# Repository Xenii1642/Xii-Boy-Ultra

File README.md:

Have you ever dreamed of a portable Wii before? Or even one with Wifi and Bluetooth integration? 
What about analog triggers, and RVL-DD? Or the Wire-free system that allows you to entirely dissasemble the system without any soldering iron?

Well, I'm here to tell that that dream came true, and I called it the Xii-Boy Ultra. 

This new Xii-Boy Ultra is the third and latest edition of my Xii-Boy design I first started almost 2 years ago. 
It comes with all the latest features everyone has been dreaming of for years. This means many crazy mods like the RVL-DD,
or all the cool stuff over the [4Layer Technologies](https://4layertech.com/), analog triggers for full Gamecube games compatibility,
optional WiFi and Bluetooth functionalities to play online or to use an original WiiMote controller and so many others. 
Everything is nicely packed up inside that little portable, 25% smaller than the previous Gboy III. 

Further technical specifications can be found on the following links:
- [Xii-Boy Ultra Worklog](https://bitbuilt.net/forums/threads/xii-boy-ultra-v3.6641/)
- [Xii-Boy Ultra Beta Release](https://bitbuilt.net/forums/threads/the-xii-boy-ultra-v3-beta-release.6918/)
- [Xii-Boy Ultra REV 2 Release](https://bitbuilt.net/forums/threads/xii-boy-ultra-rev-2.7108/#post-74825)

I've been working on the possibility to offer kits to the community for the last 7 months. 
Over that time, the design received a lot of changes to improve reliability, compatibility and overall quality of the build. 
This branche of the repository is all about the latest Revision 2 of the design. It is made with the kits in mind, and is the revision the 6 beta testers will receive for a review.

I personally assembled that latest revision by myself, and it has been confirmed working, reason why I'm sharing everything here!

⚠️ Due to the complexity nature of the build, and the knowledge it requires to build or use, I can't be held responsible for any issues, accidents or injuries that may occur. 
This Beta Reivision might also come with design flaws or issues. Please contact me of the Xii-Boy Team in case you notice any. ⚠️

# Availability
For now, the design cannot be purchased as a kit. This will hopefully change in a few months, even though I have no idea of when the kits will become available. Stay tuned on my Worklog.
This means the only alternative is to source all the parts on yourself and to assemble everything on your side. 

Please take a look at the following points carefully. 

# Parts
Everything you need to build your own can be found in the [Xii-Boy Ultra Parts list](https://github.com/Xenii1642/Xii-Boy-Ultra/blob/REV-2.0/Parts-List.pdf) file. 
Please note that most of the articles are only available through Aliexpress, which might not be ideal due to the tariffs situation.

🔋For the batteries, I personally recommend those: [Recommended Batteries](https://www.akkuteile.de/samsung-inr18650-35e-3-6v-3-7v-3500mah-pluspol-flach_100631_3391)
There is plenty of website that sell batteries. You should aquire them from a source you're confident with. If you live in Europe, I highly recommend [Akkuteile](https://www.akkuteile.de/). 
It's a German website and I always been pleased by their services. ⚠️ Be careful to order them from a reliable source to avoid counterfeiting. Fake batteries can be extremly dangerous. ⚠️

# PCBs
As all the build, the Xii-Boy Ultra PCBs are all open-sourced. If you just want to order them, you can use the [Gerber files](https://github.com/Xenii1642/Xii-Boy-Ultra/tree/REV-2.0/Gerbers).
Multiple manufacters work, but I suggest either [JLCPCB](https://jlcpcb.com/) or [PCBWay](https://pcbway.com) for that build.

You can also make edits using the [Kicad 9 files](https://github.com/Xenii1642/Xii-Boy-Ultra/tree/REV-2.0/KiCad%20Files).

For the components, everything is listed in the [PCB BOM File](https://github.com/Xenii1642/Xii-Boy-Ultra/blob/REV-2.0/PCB-BOM.pdf). 
Some articles can only be found on Digikey, reason why all the parts of this list come from them. 

Ordering PCB is one of the most important step, and you should really make sure to enable the correct settings while ordering, otherwise you could run into multiple issues.
Many of the following boards **will not** work with the default settings, so please make sure to order them with the proper settings 👍

Here is a list of all the settings for each board:
### [**Main PCB (XBU-001)**:](https://github.com/Xenii1642/Xii-Boy-Ultra/blob/REV-2.0/Gerbers/Main%20PCB.zip)
- Material: FR4
- Specify Stackup: YES
- Stackup profile: JLC04161H-7628
- Thickness: 1.6mm
  
### [**Xii-DD (XBU-002)**:](https://github.com/Xenii1642/Xii-Boy-Ultra/blob/REV-2.0/Gerbers/Xii-DD.zip)
- Material: FR4
- Thickness: 1.2mm
  
### [**Controller PCB (XBU-003)**:](https://github.com/Xenii1642/Xii-Boy-Ultra/blob/REV-2.0/Gerbers/Controller%20PCB.zip)
- Material: FR4
- Thickness: 1.6mm
- Surface finish: ENIG

### [**Xii-Flex Ultra (XBU-004)**:](https://github.com/Xenii1642/Xii-Boy-Ultra/blob/REV-2.0/Gerbers/Xii-Flex%20Ultra.zip)
- Material: Flex
- Thickness: 0.12mm (💡0.11mm also works, but it's way riskier and more fragile according to some people. I personnaly didn't notice a lot of differences.)
- Stiffener: YES, Polyimide 0.2mm

### [**Trigger PCB (XBU-005)**:](https://github.com/Xenii1642/Xii-Boy-Ultra/blob/REV-2.0/Gerbers/Trigger%20PCB.zip)
- Material: FR4
- Thickness: 1mm

### [**Xii-Strip (XBU-006)**:](https://github.com/Xenii1642/Xii-Boy-Ultra/blob/REV-2.0/Gerbers/Xii-Strip.zip)
- Material: FR4
- Thickness: 0.8mm

### [**40p Shielded FFC (XBU-007)**:](https://github.com/Xenii1642/Xii-Boy-Ultra/blob/REV-2.0/Gerbers/Shielded%20FFC.zip)
- Material: Flex
- Thickness: 0.12 (💡For that baord, 0.11mm also works well)
- Stiffener: YES, Polyimide 0.2mm

Color and can be changed, but make sure to only modify the settings you're confident with. 

# Shell
The shell files are all available in the [3D Section](https://github.com/Xenii1642/Xii-Boy-Ultra/tree/REV-2.0/3D).
Since STL can only be ordered and not edited, I decided to only share the STEP files, which allow both editing and ordering without any issues. 

Some files have minors changes, so make sure to read the following points to understand the one you need for your use.
### **FDM**:
If you have a classic FDM 3D Printer, or planned printing the case on one, you should use the [FDM](https://github.com/Xenii1642/Xii-Boy-Ultra/tree/REV-2.0/3D/Shell/FDM) version of the files.
Screen's friction fit doesn't have the same tolerances on FDM and SLS/SLA. Choosing the wrong file might occur into the screen to not fit at all, or to not stick at all, causing it to fall.

### **SLS-SLA**:
If you planned ordering the case through [JLC3DP](https://jlc3dp.com/) or [PCBWay](https://www.pcbway.com/) using Nylon (SLS or MJF) or Resin (SLA), or simply printing one yourself with a resin printer,
you should use the [Resin & Nylon](https://github.com/Xenii1642/Xii-Boy-Ultra/tree/REV-2.0/3D/Shell/SLS-SLA) file.
Considering the shell is much smoother here, normal Friction Fit doesn't work well, and the screen might pop off pretty easily.
To avoid that, those versions have a Super Friction Fit technology, which mimic the FDM layers and make the screen strongly attached into the shell.

⚠️ Disclamer: SLA + spray varnish is something to avoid, since it adds enough volume to make the parts to not fit properly. 

### **Stands**
You can also find the Xii-Boy Ultra stands in the [stands folder](https://github.com/Xenii1642/Xii-Boy-Ultra/tree/REV-2.0/3D/Stands) or on my Printables account: [Xii-Boy Ultra stands - Printables](https://www.printables.com/model/1307105-xii-boy-ultra-stands)
One of them has a slot for the [XiiSBar](https://github.com/Xenii1642/XiiSBar), which allows you to play game with the IR pointer (original WiiMote pointing system)

# Software
The Xii-Boy Ultra runs on RVLoader, a wonderful homebrew app made by Aurelio over the BitBuilt forum. However, it needs to be slightly modified for all the Xii-Boy Ultra features to work properly.

You'll find all the new files you need to update in the [Software](https://github.com/Xenii1642/Xii-Boy-Ultra/tree/REV-2.0/Software) section of the repository.

⚠️ Those files are tempoary and have been modified for the Xii-Boy Ultra only. They might contain issues or instablities. Update at your own risks. ⚠️
### [GCPlus2.0Update.hex](https://github.com/Xenii1642/Xii-Boy-Ultra/blob/main/Software/GCPlus2.0Update.hex)
This file is used to update the GC+ 2 from [4LayerTech](https://4layertech.com/) with a new version compatible with the Xii-Boy Ultra analog trigger system.
To update your GC+ 2.0, simply copy/paste that file in the root of your Xii-Boy Ultra µSD card.

### [boot.dol](https://github.com/Xenii1642/Xii-Boy-Ultra/blob/main/Software/boot.dol):
This files is used to add Volume and Brightness over buttons in Gamecube games.
To add those features, simply drag and replace the original file in `/apps/Nintendont`.

### [LCDDriver.bit](https://github.com/Xenii1642/Xii-Boy-Ultra/blob/main/Software/LCDDriver.bit)
This file is used to flash the DD software when booting. The original one, present by default in RVLoader contains a little issue with i2C.
It results into random crashes and volume or brightness control interferances. This file also removes the whine coil noise the old DD bitstream caused.
To install it, you just have to replace the original file in the root of your µSD card. ⚠️ This file or the previous one is necessary for the portable to boot ⚠️

### [hud.elf](https://github.com/Xenii1642/Xii-Boy-Ultra/blob/main/Software/hud.elf)
Like boot.dol, this file is used to add Volume and Brightness over buttons in Wii games.
To add those features, simply drag and replace the original file in `/rvloader/Hiidra/modules`

Once everything has been installed, safety eject your µSD card / Xii-Boy Ultra console.
Boot it up and go to `Settings` --> `Controller` --> `Firmware Update`
If everything has been done correctly, your Xii-Boy Ultra should be udpated.
Set your `Triggers mode` to `Analog` and press `Save Config`
Reboot your device and go to `Settings` --> `Controller` --> `Buttons Tester`
You should now see all the buttons and the analog triggers working!

# General Software Setting:
- In `Power` --> `Charge Settings`, `Battery Capacity` needs to be set at 7000mAh (or the capacity of one cell *2 `3500mAh *2 = 7000mAh`)
- `Charging Current` should be set at 3520mA
- `Precharge` and `Termination current` should be set at 128mA
- `Charge Voltage` should be set at 4200mV
- In `Misc Settings`, you need to change `Status LED type:` to `Adressable Type B`
- in `Audio`, `Volume control system` needs to be set to Buttons.
💡You can adapt all the settings depends on you. I personally set the `Status LED Intensity` to 5 and the `Rumble Intensity` to 60.

💡Make sure to test all the features, you should launch a Wii and a GameCube game, to make sure everything is working fine.

# Revisions
- REV0 - 1/1/2025 (First prototype not available)
- [REV1](https://github.com/Xenii1642/Xii-Boy-Ultra/tree/REV-1.0) - 18/5/2025 (Fixes the previous issues, first released revision)
- [REV2](https://github.com/Xenii1642/Xii-Boy-Ultra/tree/REV-2.0) - 16/11/2025 CURRENT (Fixes all the previous issues, removes pogo pins and upgrade a lot the reliability)

# Credits
Time to mention everybody who helped along the project!
- The Xii-Boy Team (JamesPi, BryceShaw, and I)
- YveltalGriffin (Help about PCB Design)
- Aurelio (RVLoader devloppement and software help) 
- All the Beta Testers (Modding Marius, Supertazon, YveltalGriffin, Macho Nacho, JamesPi, JoshsJunk05) 👍
  
# License
All Xii-Boy Ultra revisions are released under the CERN-OHL-S-2.0 license. 
This license allows you to:
- Study
- Modify
- Manufacture
- Sell
- Distribute

Any modified versions of derivatives must also remain open-source under **the same, unmodified license**
You must also properly credit the original creators when reusing or redistributing these files.

# Support
Due to the early Beta Release of the Xii-Boy Ultra, the design might contain issues, design flaws or other things.
This new REV2 corrected **all** the issues the previous revision had. But it doesn't mean it doesn't contain any. 

If you notice any issues, or things that could/should me updated, or even general recommendation, feel free to reach out for letting me know.
You can also ask help over the BitBuilt community (Discord server or forums), and I'd be happy to help. 

I'd also be grateful to receive feeback of the design. You can freely say what you thought about it, what you liked, disliked, etc.

Thanks a lot for the support and the help! Your feeback help a lot to make this product as perfect as possible!

I wish you all the best. Have fun!

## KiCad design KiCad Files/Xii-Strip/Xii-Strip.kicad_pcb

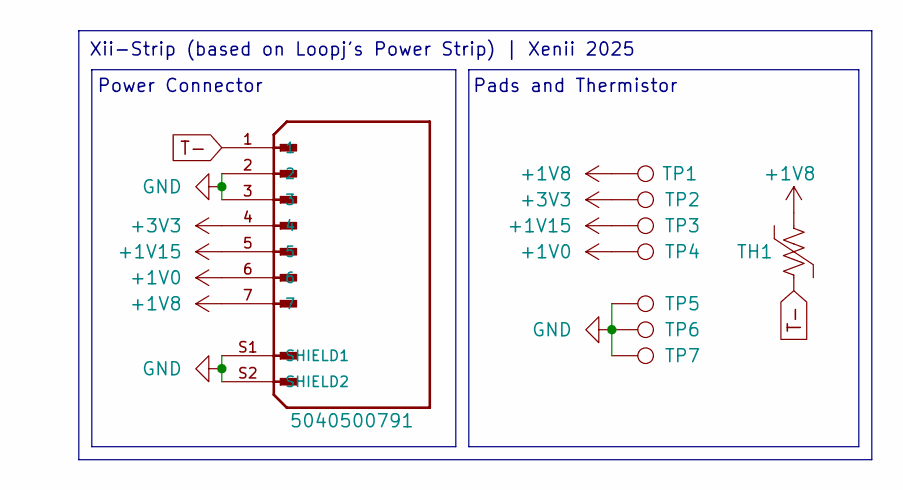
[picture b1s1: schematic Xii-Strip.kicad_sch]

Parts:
J1: 5040500791; MOLEX_5040500791; PARTREV B
TH1: Thermistor_US; R_0603_1608Metric
TP1, TP2, TP3, TP4, TP5, TP6, TP7: TestPoint; Xii-Strip-Power-Pad

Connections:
+1V0: J1.6, TP4.1
+1V8: J1.7, TH1.2, TP1.1
+1V15: J1.5, TP3.1
+3V3: J1.4, TP2.1
GND: J1.2, J1.3, J1.S1 (SHIELD1), J1.S2 (SHIELD2), TP5.1, TP6.1, TP7.1
T-: J1.1, TH1.1

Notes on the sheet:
Power Connector
Xii-Strip (based on Loopj's Power Strip) | Xenii 2025
Pads and Thermistor

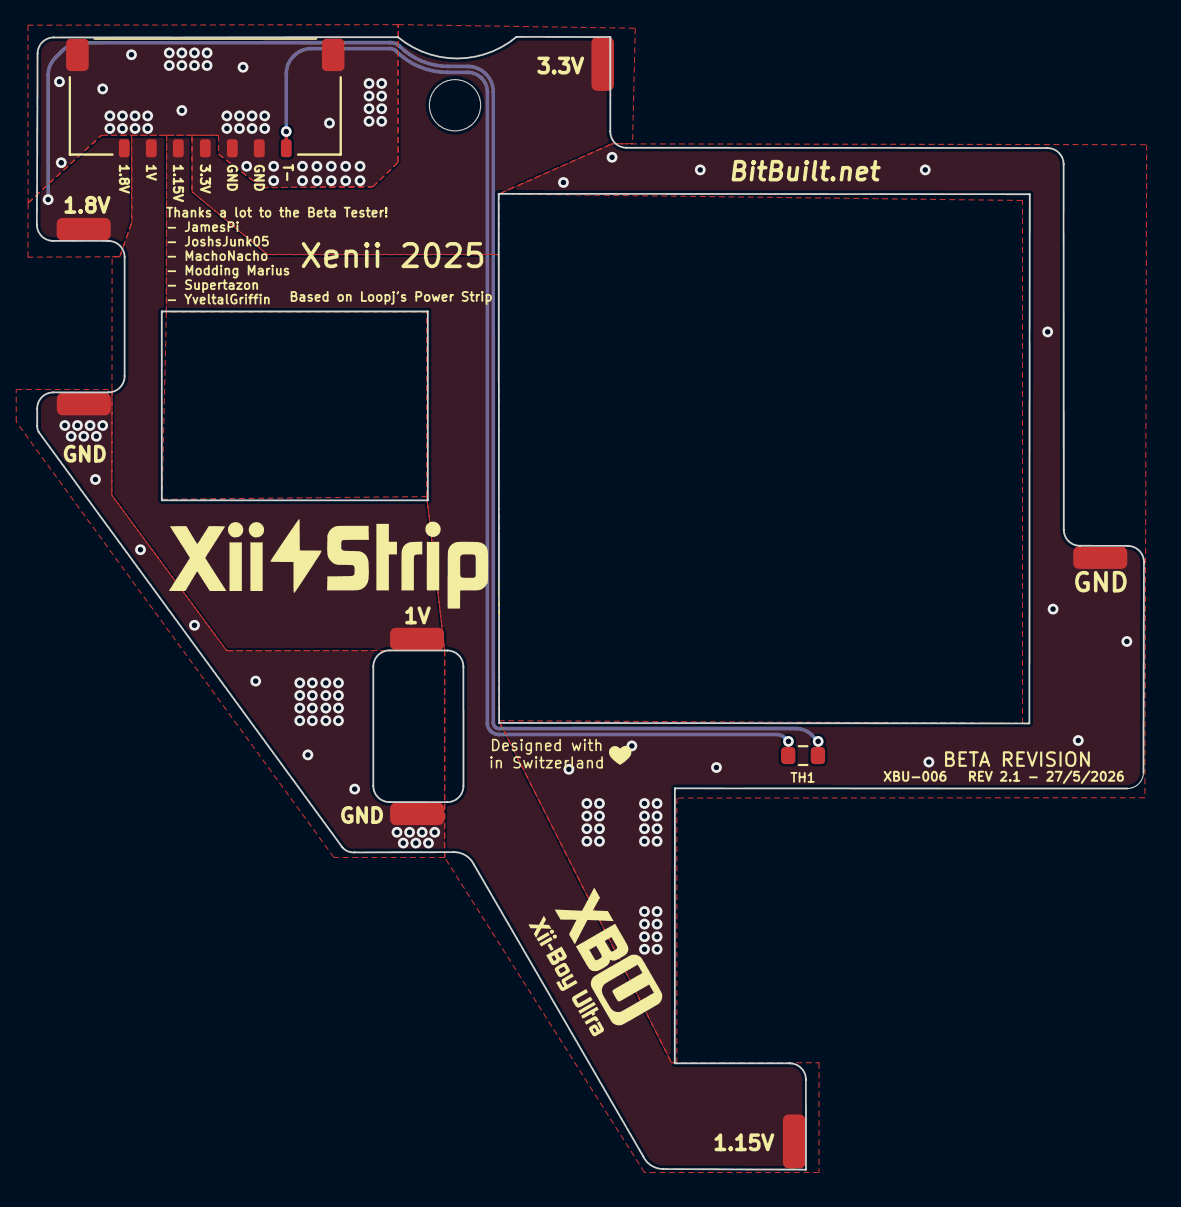
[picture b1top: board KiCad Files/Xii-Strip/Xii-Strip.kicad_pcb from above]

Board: 2 copper layers, 61.5 x 62.9 mm, 9 parts (0 on the bottom side), 6 nets.

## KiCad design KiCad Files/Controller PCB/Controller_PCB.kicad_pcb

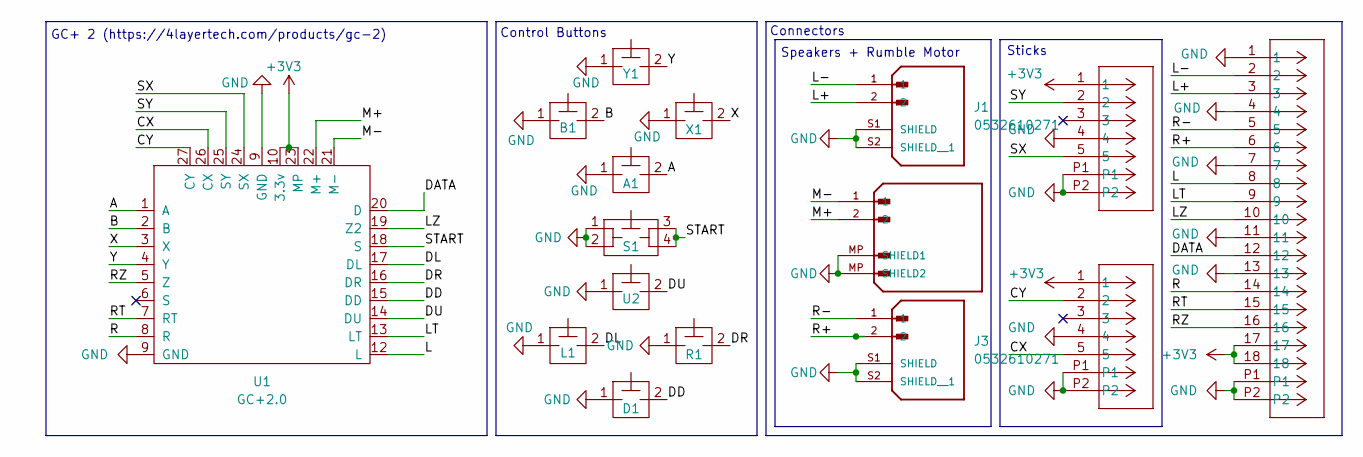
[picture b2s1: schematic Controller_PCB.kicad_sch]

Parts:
A1: DSLPad-Final
B1: DSLPad-Final
D1: DSLPad-Final
J1, J3: 0532610271; MOLEX_0532610271; PARTREV J
J2: 5037630291; MOLEX_5037630291; PARTREV B
J4, J5: 5051100592; CON_5051100592_MOL
J7: 5051101892; CON_5051101892_MOL
L1: DSLPad-Final
R1: DSLPad-Final
S1: SW_TL3315NF250Q
U1: GC+2.0
U2: DSLPad-Final
X1: DSLPad-Final
Y1: DSLPad-Final

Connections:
+3V3: J4.1, J5.1, J7.17, J7.18, U1.10 (3.3v), U1.23 (MP)
/A: A1.2, U1.1 (A)
/B: B1.2, U1.2 (B)
/CX: J5.5, U1.26 (CX)
/CY: J5.2, U1.27 (CY)
/DATA: J7.12, U1.20 (D)
/DD: D1.2, U1.15 (DD)
/DL: L1.2, U1.17 (DL)
/DR: R1.2, U1.16 (DR)
/DU: U1.14 (DU), U2.2
/L: J7.8, U1.12 (L)
/L+: J1.2, J7.3
/L-: J1.1, J7.2
/LT: J7.9, U1.13 (LT)
/LZ: J7.10, U1.19 (Z2)
/M+: J2.2, U1.22 (M+)
/M-: J2.1, U1.21 (M-)
/R: J7.14, U1.8 (R)
/R+: J3.2, J7.6
/R-: J3.1, J7.5
/RT: J7.15, U1.7 (RT)
/RZ: J7.16, U1.5 (Z)
/START: S1.3, S1.4, U1.18 (S)
/SX: J4.5, U1.24 (SX)
/SY: J4.2, U1.25 (SY)
/X: U1.3 (X), X1.2
/Y: U1.4 (Y), Y1.2
GND: A1.1, B1.1, D1.1, J1.S1 (SHIELD), J1.S2 (SHIELD__1), J2.MP (SHIELD1), J3.S1 (SHIELD), J3.S2 (SHIELD__1), J4.4, J4.P1, J4.P2, J5.4, J5.P1, J5.P2, J7.1, J7.4, J7.7, J7.11, J7.13, J7.P1, J7.P2, L1.1, R1.1, S1.1, S1.2, U1.9 (GND), U2.1, X1.1, Y1.1

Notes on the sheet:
GC+ 2 (https://4layertech.com/products/gc-2)
Speakers + Rumble Motor
Sticks
Control Buttons
Connectors

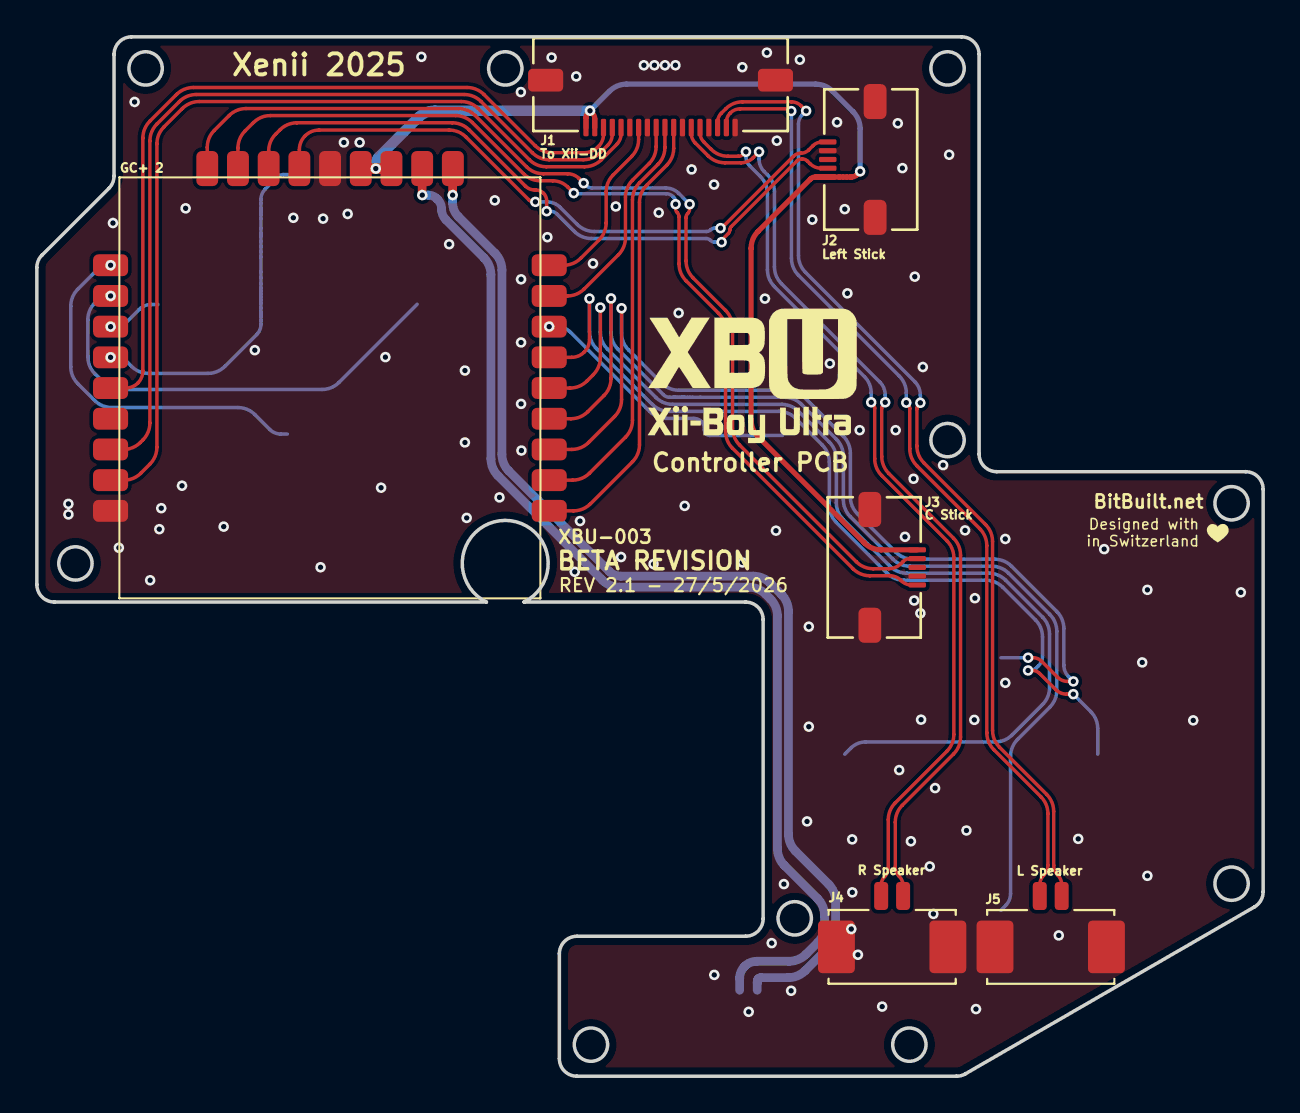
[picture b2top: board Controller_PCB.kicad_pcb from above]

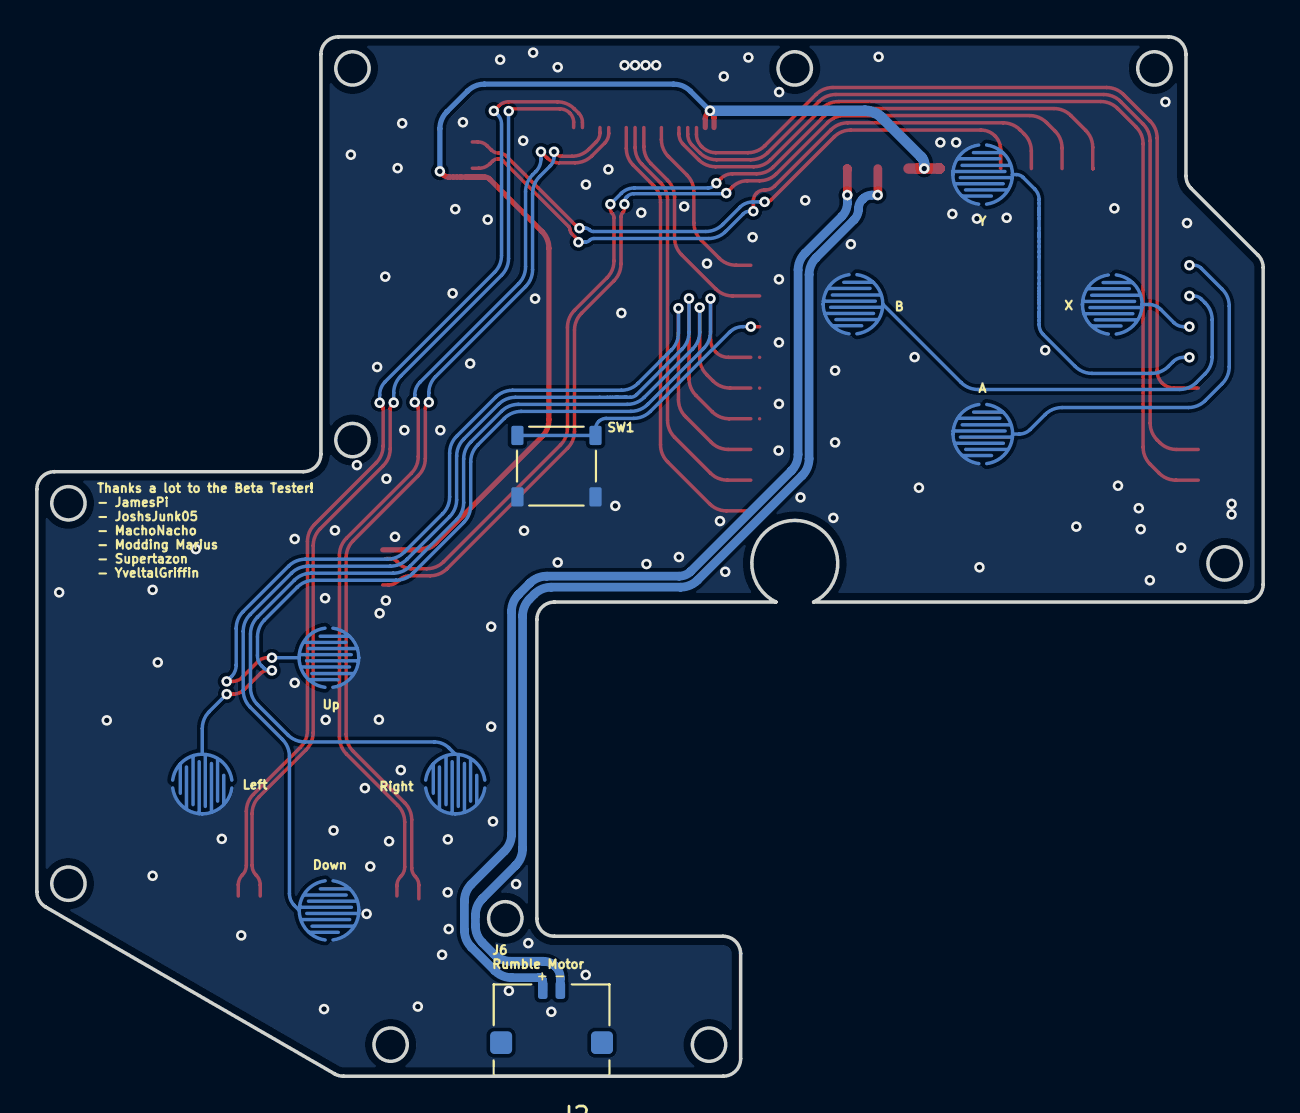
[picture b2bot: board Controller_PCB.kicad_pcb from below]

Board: 2 copper layers, 69.9 x 59.2 mm, 16 parts (10 on the bottom side), 28 nets.

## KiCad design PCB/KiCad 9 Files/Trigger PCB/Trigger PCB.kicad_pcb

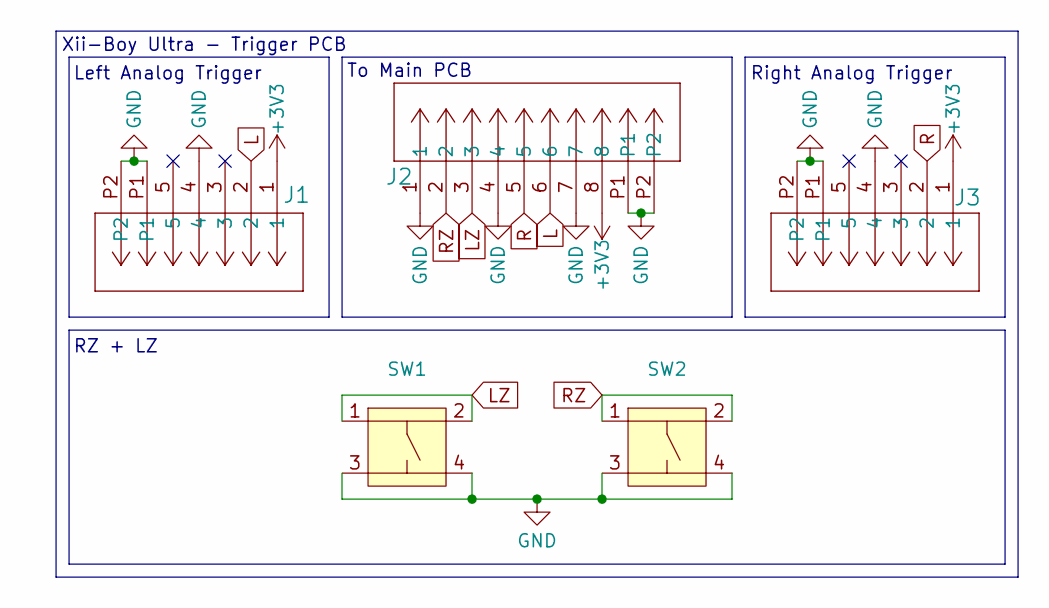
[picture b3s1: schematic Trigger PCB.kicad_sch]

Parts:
J1, J3: 5051100592; CON_5051100592_MOL
J2: 5051100892; CON_5051100892_MOL
SW1, SW2: KS201G

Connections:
+3V3: J1.1, J2.8, J3.1
GND: J1.4, J1.P1, J1.P2, J2.1, J2.4, J2.7, J2.P1, J2.P2, J3.4, J3.P1, J3.P2, SW1.3, SW1.4, SW2.3, SW2.4
L: J1.2, J2.6
LZ: J2.3, SW1.1, SW1.2
R: J2.5, J3.2
RZ: J2.2, SW2.1, SW2.2

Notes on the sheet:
RZ + LZ
Left Analog Trigger
To Main PCB
Xii-Boy Ultra - Trigger PCB
Right Analog Trigger

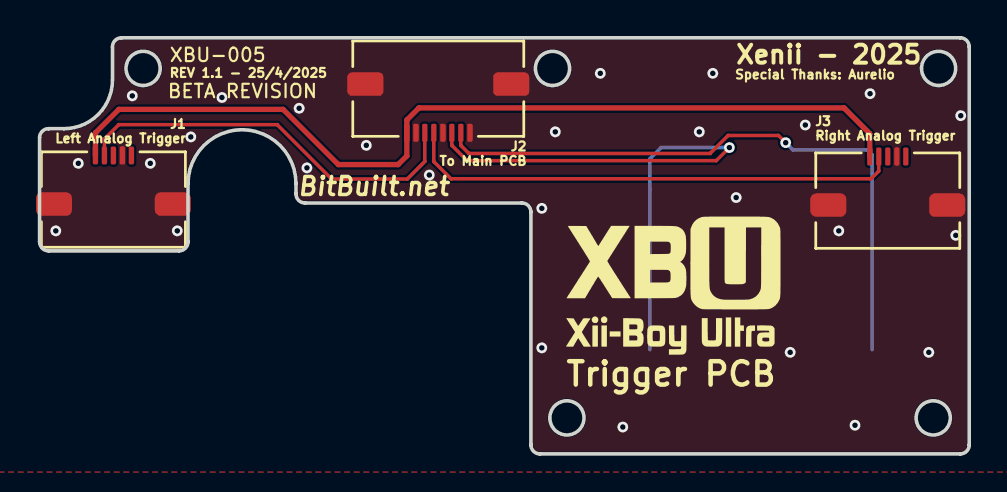
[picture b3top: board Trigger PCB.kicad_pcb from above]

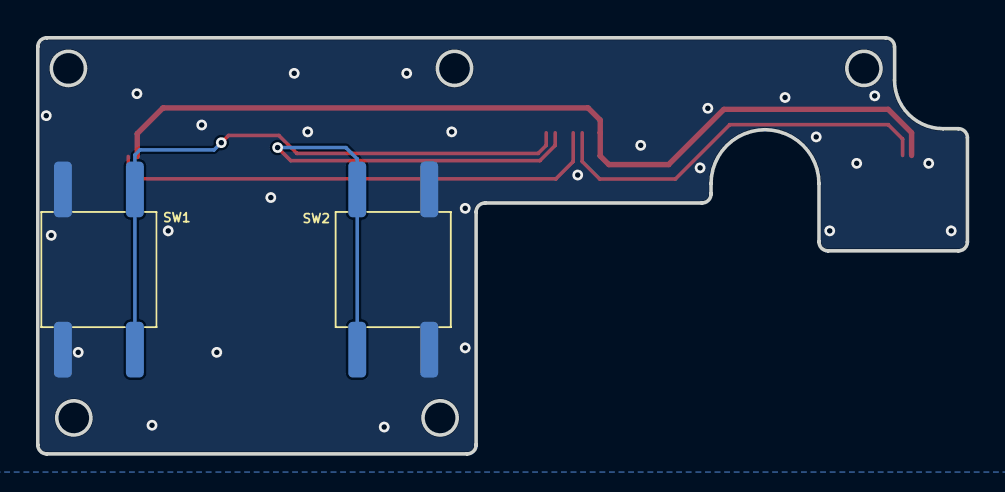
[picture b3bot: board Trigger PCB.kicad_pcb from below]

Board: 2 copper layers, 51.6 x 23.1 mm, 5 parts (2 on the bottom side), 6 nets.

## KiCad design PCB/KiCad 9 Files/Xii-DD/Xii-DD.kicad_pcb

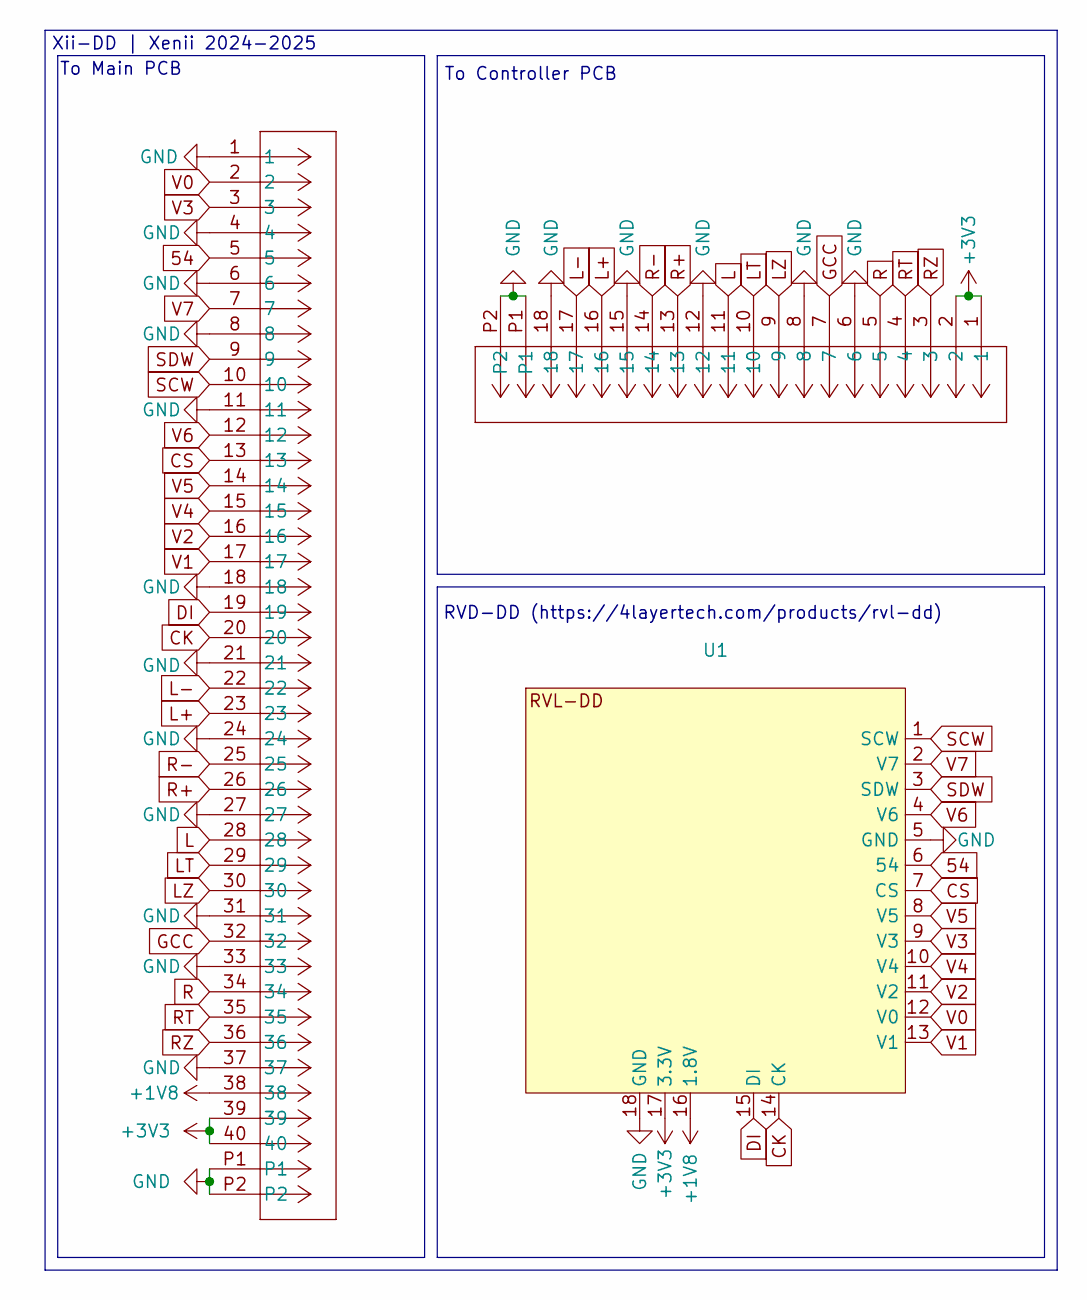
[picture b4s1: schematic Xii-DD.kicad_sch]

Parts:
J1: 5051104091; CON_5051104091_MOL
J3: 5051101892; CON_5051101892_MOL
U1: RVLDD_Pads

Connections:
54: J1.5, U1.6 (54)
+1V8: J1.38, U1.16 (1.8V)
+3V3: J1.39, J1.40, J3.1, J3.2, U1.17 (3.3V)
CK: J1.20, U1.14 (CK)
CS: J1.13, U1.7 (CS)
DI: J1.19, U1.15 (DI)
GCC: J1.32, J3.7
GND: J1.1, J1.4, J1.6, J1.8, J1.11, J1.18, J1.21, J1.24, J1.27, J1.31, J1.33, J1.37, J1.P1, J1.P2, J3.6, J3.8, J3.12, J3.15, J3.18, J3.P1, J3.P2, U1.5 (GND), U1.18 (GND)
L: J1.28, J3.11
L+: J1.23, J3.16
L-: J1.22, J3.17
LT: J1.29, J3.10
LZ: J1.30, J3.9
R: J1.34, J3.5
R+: J1.26, J3.13
R-: J1.25, J3.14
RT: J1.35, J3.4
RZ: J1.36, J3.3
SCW: J1.10, U1.1 (SCW)
SDW: J1.9, U1.3 (SDW)
V0: J1.2, U1.12 (V0)
V1: J1.17, U1.13 (V1)
V2: J1.16, U1.11 (V2)
V3: J1.3, U1.9 (V3)
V4: J1.15, U1.10 (V4)
V5: J1.14, U1.8 (V5)
V6: J1.12, U1.4 (V6)
V7: J1.7, U1.2 (V7)

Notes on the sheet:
RVD-DD (https://4layertech.com/products/rvl-dd)
To Main PCB
Xii-DD | Xenii 2024-2025
To Controller PCB

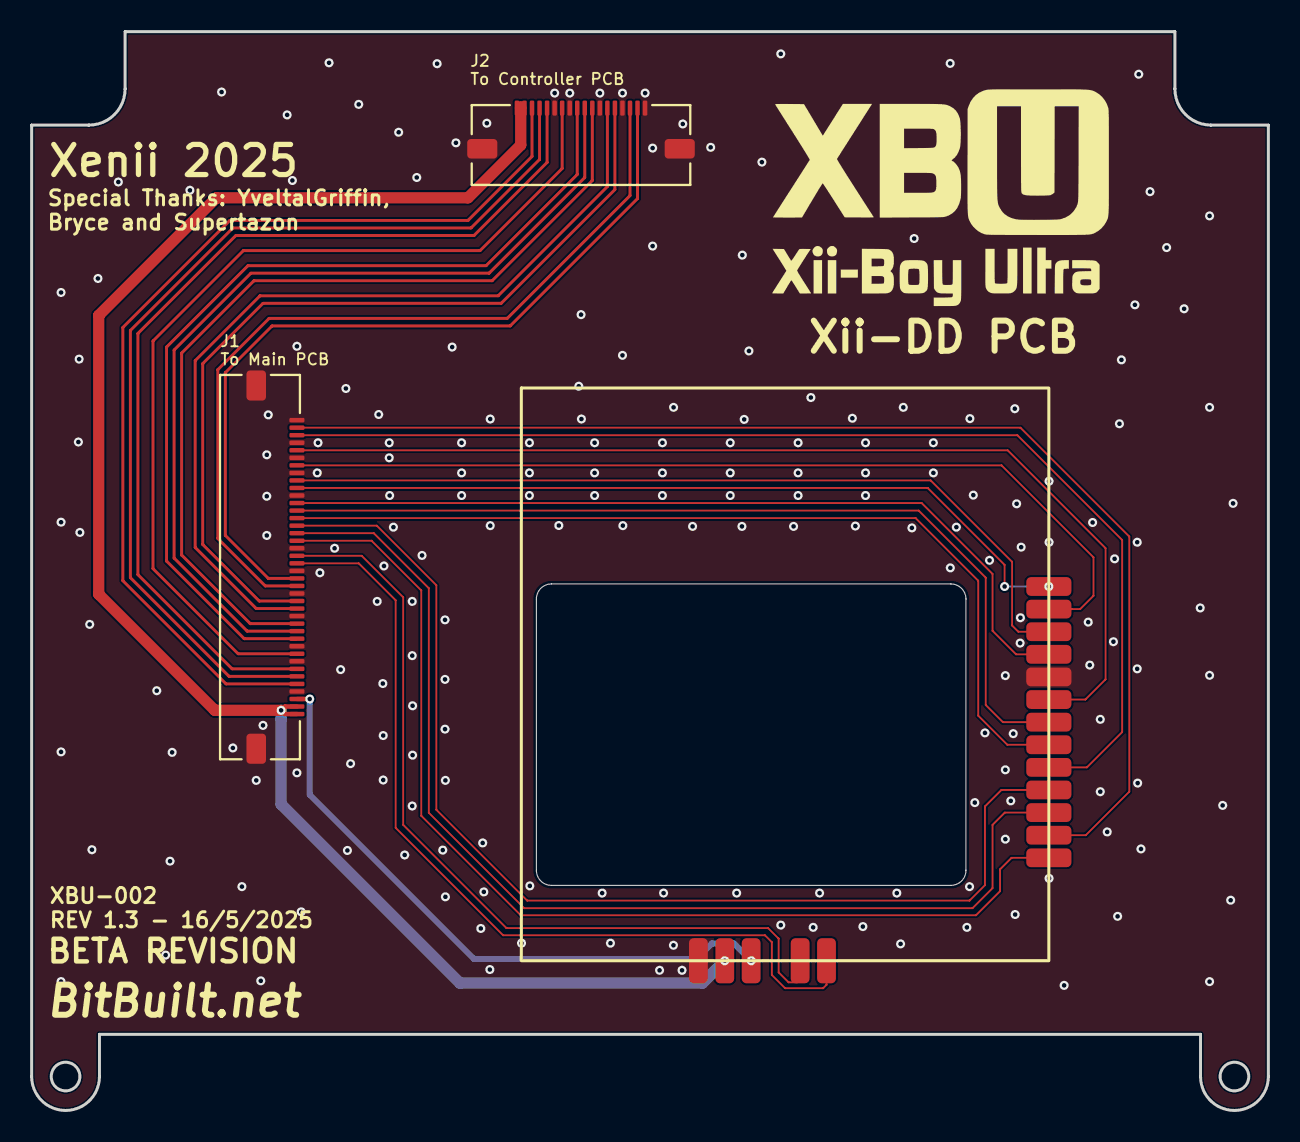
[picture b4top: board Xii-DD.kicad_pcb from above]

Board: 2 copper layers, 82.0 x 71.6 mm, 3 parts (0 on the bottom side), 28 nets.

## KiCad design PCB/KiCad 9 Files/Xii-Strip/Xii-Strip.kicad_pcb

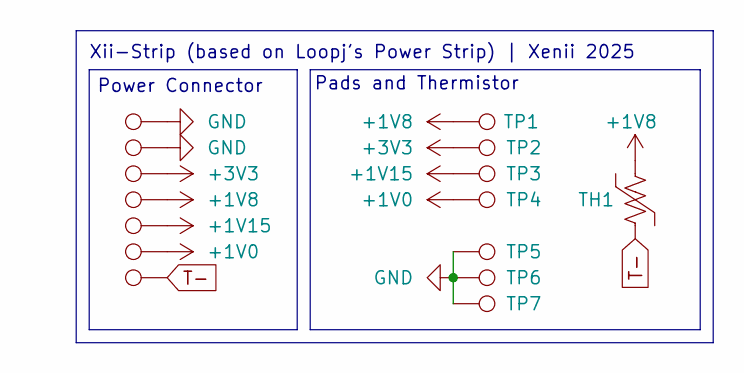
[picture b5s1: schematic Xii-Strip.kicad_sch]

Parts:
TH1: Thermistor_US; R_0603_1608Metric
TP1, TP2, TP3, TP4, TP5, TP6, TP7: TestPoint; Xii-Strip-Power-Pad
TP8, TP10, TP11, TP12, TP13: TestPoint; Pogo Power Pad Dual
TP9, TP14: TestPoint; Power-POGO

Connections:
+1V0: TP4.1, TP11.1
+1V8: TH1.2, TP1.1, TP13.1
+1V15: TP3.1, TP10.1
+3V3: TP2.1, TP8.1
GND: TP5.1, TP6.1, TP7.1, TP12.1, TP14.1
T-: TH1.1, TP9.1

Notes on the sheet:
Power Connector
Xii-Strip (based on Loopj's Power Strip) | Xenii 2025
Pads and Thermistor

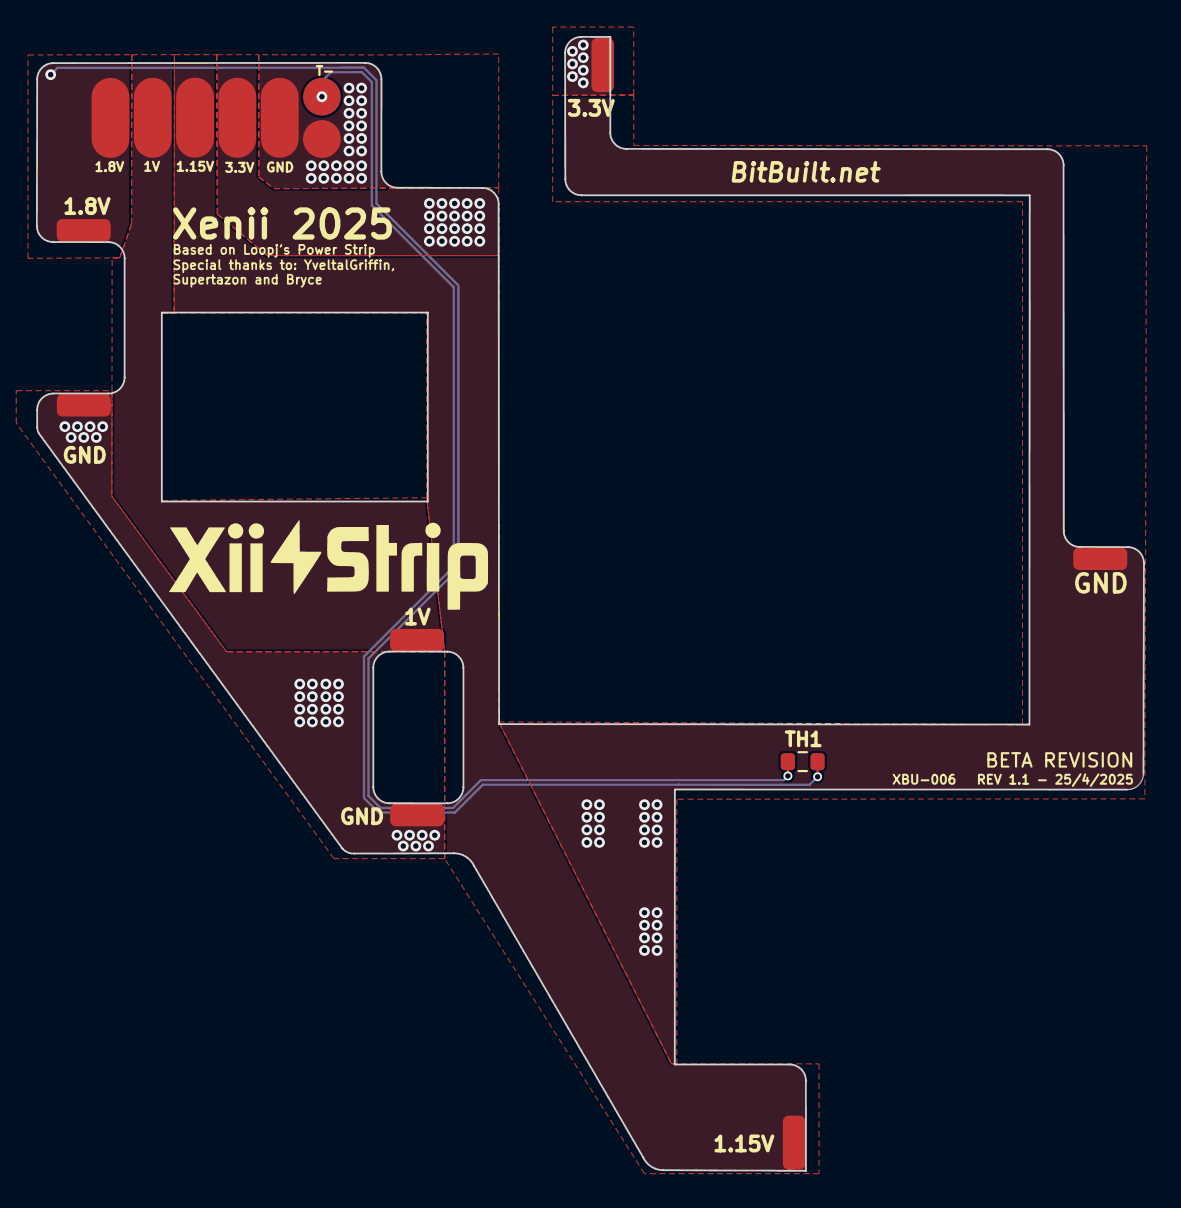
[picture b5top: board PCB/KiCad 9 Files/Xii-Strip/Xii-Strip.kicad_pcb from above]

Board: 2 copper layers, 61.5 x 63.0 mm, 15 parts (0 on the bottom side), 6 nets.

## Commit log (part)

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2025-05-17 README.md
2025-05-17 Adding KiCad 9 PCB files
2025-05-17 Rename XBU-BR Light.png to XBU-BR-Light.png
2025-05-21 Small spelling and name corrections
2025-05-23 README.md
    Corrected some mistakes Sussy-OS noticed 👍
2025-09-18 README.md
    Adding new DD bitstream that removes the whine coil noise.
2025-11-15 Update README.md
    Removed image tags and related HTML from README.
2025-11-15 Rename Xii-FLex Ultra.zip to Xii-Flex Ultra.zip
2025-11-15 Enhance README with additional images
    Added images to README for visual representation.
2025-11-15 Revise images and add new content in README
    Updated image references and added new images to README.
2025-11-15 Revise README for Xii-Boy Ultra features and guidance
    Updated the README.md to include new features, specifications, and instructions for the Xii-Boy Ultra. Enhanced clarity and organization of information regarding parts, software, and assembly guidanc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
2025-11-16 Fix link description for SLS-SLA file usage
2025-11-16 Add credits section to README
    Added a credits section to acknowledge contributors and supporters.
2025-11-16 Fix links for Xii-Boy Ultra specifications
    Updated links for Xii-Boy Ultra resources in README.
2025-11-16 Fix link format for 4Layer Technologies
    Updated link format for 4Layer Technologies in README.
2025-12-28 Rename LCDDriver(7).bit to LCDDriver.bit
2026-03-12 Update which fixes some issues
2026-03-30 Add LICENSE file with CC BY-SA 4.0 license
    Added Creative Commons Attribution-ShareAlike 4.0 International Public License to the project.
2026-05-15 Add CERN Open Hardware Licence Version 2
    Added the CERN Open Hardware Licence Version 2 - Strongly Reciprocal to the project.
2026-05-15 Add license section to README
    Added license information for Matterhorn 64 CORE.
2026-05-15 Fix license section header in README.md
    Updated the license section formatting in README.md.
2026-05-17 Add disclamer about SLA shells with spray varnish finish.
2026-06-28 Update README to include credit for original creators
    Added credit requirement for reuse and redistribution.
